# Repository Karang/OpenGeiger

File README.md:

OpenGeiger
==========

English :

A Bluetooth Geiger-Müller counter for everyone !

This project's aim is to developp an open-source (hardware and software) Geiger-Müller counter, open, simple, low cost, connected through bluetooth to smartphones or PC and reliable.

Because like the numerous projects started after Fukushima's accident, we want to provide the citizens a mean to make their own environmental measurement of radioactivity.

Link to our wiki : http://wiki.pmclab.fr/doku.php?id=wiki:projets:smartphone-geiger

Link to our website : http://bluegeiger.org/

Français :

Un compteur Geiger-Müller Bluetooth pour tous !

Le but de ce projet est de développer un compteur Geiger-Müller open-source (hardware et software), libre, simple, peu cher, connecté en bluetooth à des smartphones ou PC, et fiable.

Car après laccident de Fukushima, de nombreuses initiatives sont apparues pour permettre à chacun de réaliser ses propres mesures citoyennes de radioactivité ambiante.

Lien vers le wiki : http://wiki.pmclab.fr/doku.php?id=wiki:projets:smartphone-geiger

Lien vers le site : http://bluegeiger.org/

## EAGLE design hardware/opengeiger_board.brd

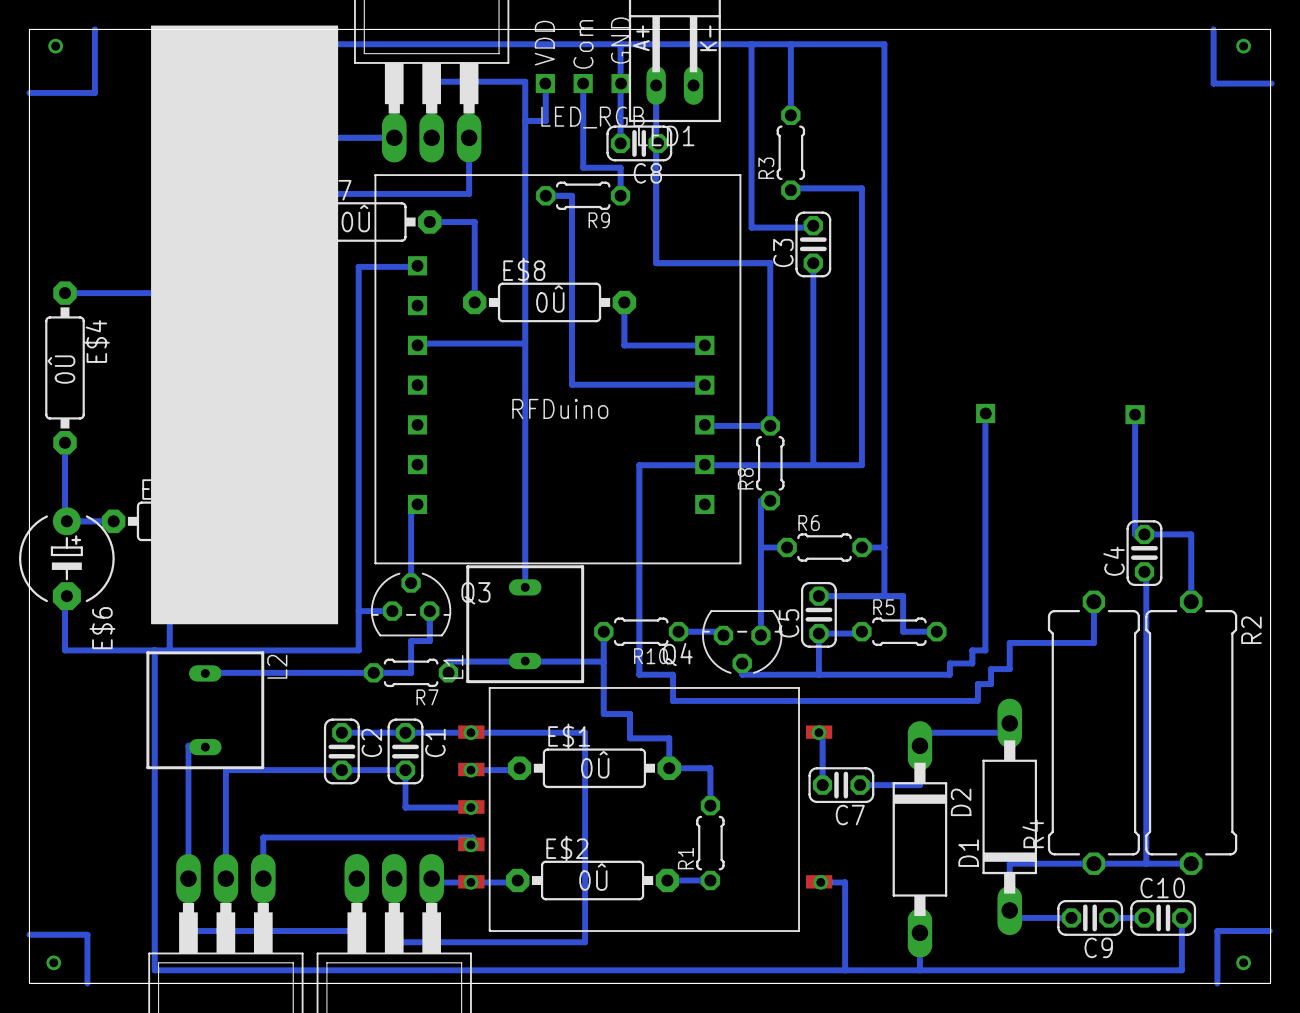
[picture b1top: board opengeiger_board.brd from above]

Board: 2 copper layers, 84.3 x 64.8 mm, 44 parts (0 on the bottom side), 13 nets.

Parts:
C1, C2, C3, C5, C6, C8, C10: 100n; C025-024X044
C4: 10n; C025-024X044
C7, C9: 47n; C025-024X044
D1, D2: 1N5060GP; DO15-12
E$1, E$2, E$3, E$4, E$7, E$8: 0R/10
E$6: E5-6
L1, L2: 100u; SD8
LED1: Q62902-B155
Q1, Q2: BU505; TO220
Q3, Q4: BC337; TO92
R1, R8, R10: 330; 0204/5
R2, R4: 4.7M; 0617/17
R3: 27k; 0204/5
R5: 490k; 0204/5
R6, R11: 10k; 0204/5
R7, R9: 1k; 0204/5
R12: 33k; 0204/5
REG: TO220
U$1: CCFL_TRANSFO
U$2: RFDUINO
U$3: TUBE
U$4: LED_RBG; LED_RGB
U$5: CHARGEUR

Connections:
unnamed: Q1.3, Q2.3
unnamed: C3.2, C5.2, C8.2, C10.2, E$4.1, LED1.K, Q3.3, R5.2, R6.2, REG.1, U$5.P$1
unnamed: C1.2, C2.2
unnamed: C9.2, D1.C, R2.2, R4.1
unnamed: C5.1, Q4.2, R5.1
unnamed: Q4.3, R8.1
unnamed: E$3.2, R11.2, REG.3, U$5.P$5
unnamed: C3.1, R3.1
unnamed: LED1.A, R8.2
unnamed: Q3.1, R7.2
S$5: E$2.2, R1.1
S$8: C4.2, U$3.P$1
VDD_BOBINE: E$1.2, R7.1, R10.2

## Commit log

2014-06-04 Add RfDuino sources
2014-06-20 Add schematic
2014-06-20 Revert "Add schematic"
    This reverts commit 64ef296e22c66ff192e51e8df23e175b54a60571.
2014-06-20 Add Board
2014-06-24 Add the battery monitor
2014-06-24 Add voltage diviser for the battery monitor
2014-06-24 Add english version of readme
2014-06-25 Add Eagle Library
2014-06-25 Revert "Add"
    This reverts commit e1762064b92fdd1ccdee8e5d888808837e14bb9b.
2014-06-26 Fix Advertisement error
2014-06-30 Change pin numbers
2014-07-01 Adjust voltage divider
2014-07-01 Add Scematic
2014-07-03 Add the .blend file of the box
2014-07-04 Make .stl files for 3D printing
2014-07-06 Unzip openGeiger.lbr + Add Eagle lib for RFD22301
2014-07-08 Add commentary
2014-07-09 ADD LED PULSE
2014-10-18 OG_KIT
    *Gerber Files
    *Board
    *Schematic
2014-10-18 Revert "OG_KIT"
    This reverts commit 87c7355799fa15c808e2c485c3de2532067464f3.
2014-10-18 OG_KIT_Final
    *Les fichiers gerbers
    *Fichier d'Eagle pour le schéma
    *Fichier d'Eagle pour la plaque
    *Une .txt contenant les noms des composants
    *Une photo de la plaque
    *Une photo de la schéma
2014-11-05 OG_CMS
    Circuit avec les mauvaises dimentions.
2014-11-10 Addition du DutyCycle dans les infos transmises
    Addition du DutyCycle dans les infos transmises. Calqué sur la tension
    et le nombre de coups.
2014-11-10 Modification ordre envoi des données
    pwm puis tension puis count
2014-11-10 Amélioration de l'encodage des paquets
2014-11-11 Transmission du pwn_duty_cycle
    Plusieurs essais pour obtenir un int qui soit correctement transmis.
    Résultat : le pwm_duty_cycle (pic) transmis précisément toutes les 1000
    ms varie beaucoup. Il faudrait calculer le avg_pdc sur 2 à 4s…
2014-11-11 Tests de transfert de avg_pwm_duty_cycle
2014-11-11 Ajout de la transmission de la HT actuelle
    Ajout de actual_tension parmi les données transmises.
2014-11-12 A enlever
2014-11-12 Revert 4bbc8a8..464dcf8
    This rolls back to commit 4bbc8a88c3325f31478dbba6e71b515812978389.
2014-11-12 Fix negative dutycycle
2014-11-12 pwm_duty_cycle turned into float (was int)
2014-11-12 start using a timer in counter mode
2014-11-12 Fix leds
2014-11-15 Usage des PPI pour count/follow
2014-11-19 Remplacement ref_tension -> set_tension
